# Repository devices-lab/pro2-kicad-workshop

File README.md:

# PCB design walkthrough with KiCad workshop

## Tasks

You are given the task of extending the solder:bit Gamepad boards with more NeoPixels. A design review has highlighted that we need more blinking lights than the 5x5 LED matrix on the micro:bit can supply!

1. Download the existing design files by cloning this repository.
2. Get familiar with the NeoPixel (WS2812B) datasheet and the exisiting schematic for version 0.5.
3. Open up KiCad, and begin with the Schematic Editor - adding symbols, assiginging footprints, adding values, etc.
4. Move onto the PCB Editor and import the changes from the schematic - moving footprints, routing, zone filling, DRC, etc.
5. Build a bill of materials (BOM) and a set of Gerber fabrication files for the next workshop!
6. Use Git for version control of your KiCad project.

Don’t worry if you don’t manage to get all the steps here completed, as we also supply a set of completed production files (BOM and Gerber files) in the same repository which can be used for the next session.

## Handy web links

- [solder:bit Gamepad repository](https://github.com/devices-lab/solderbit-gamepad)
- [KiCad 8.0 documentation](https://docs.kicad.org/8.0/en/)
- [Git cheat sheet](https://education.github.com/git-cheat-sheet-education.pdf)

## Credits

Thanks to [Dr John Vidler](https://github.com/JohnVidler) and [Aron Eggens](https://github.com/mac-aron), the Computing and Communications departement at Lancaster University, and everyone at the [Devices Lab](https://github.com/devices-lab).

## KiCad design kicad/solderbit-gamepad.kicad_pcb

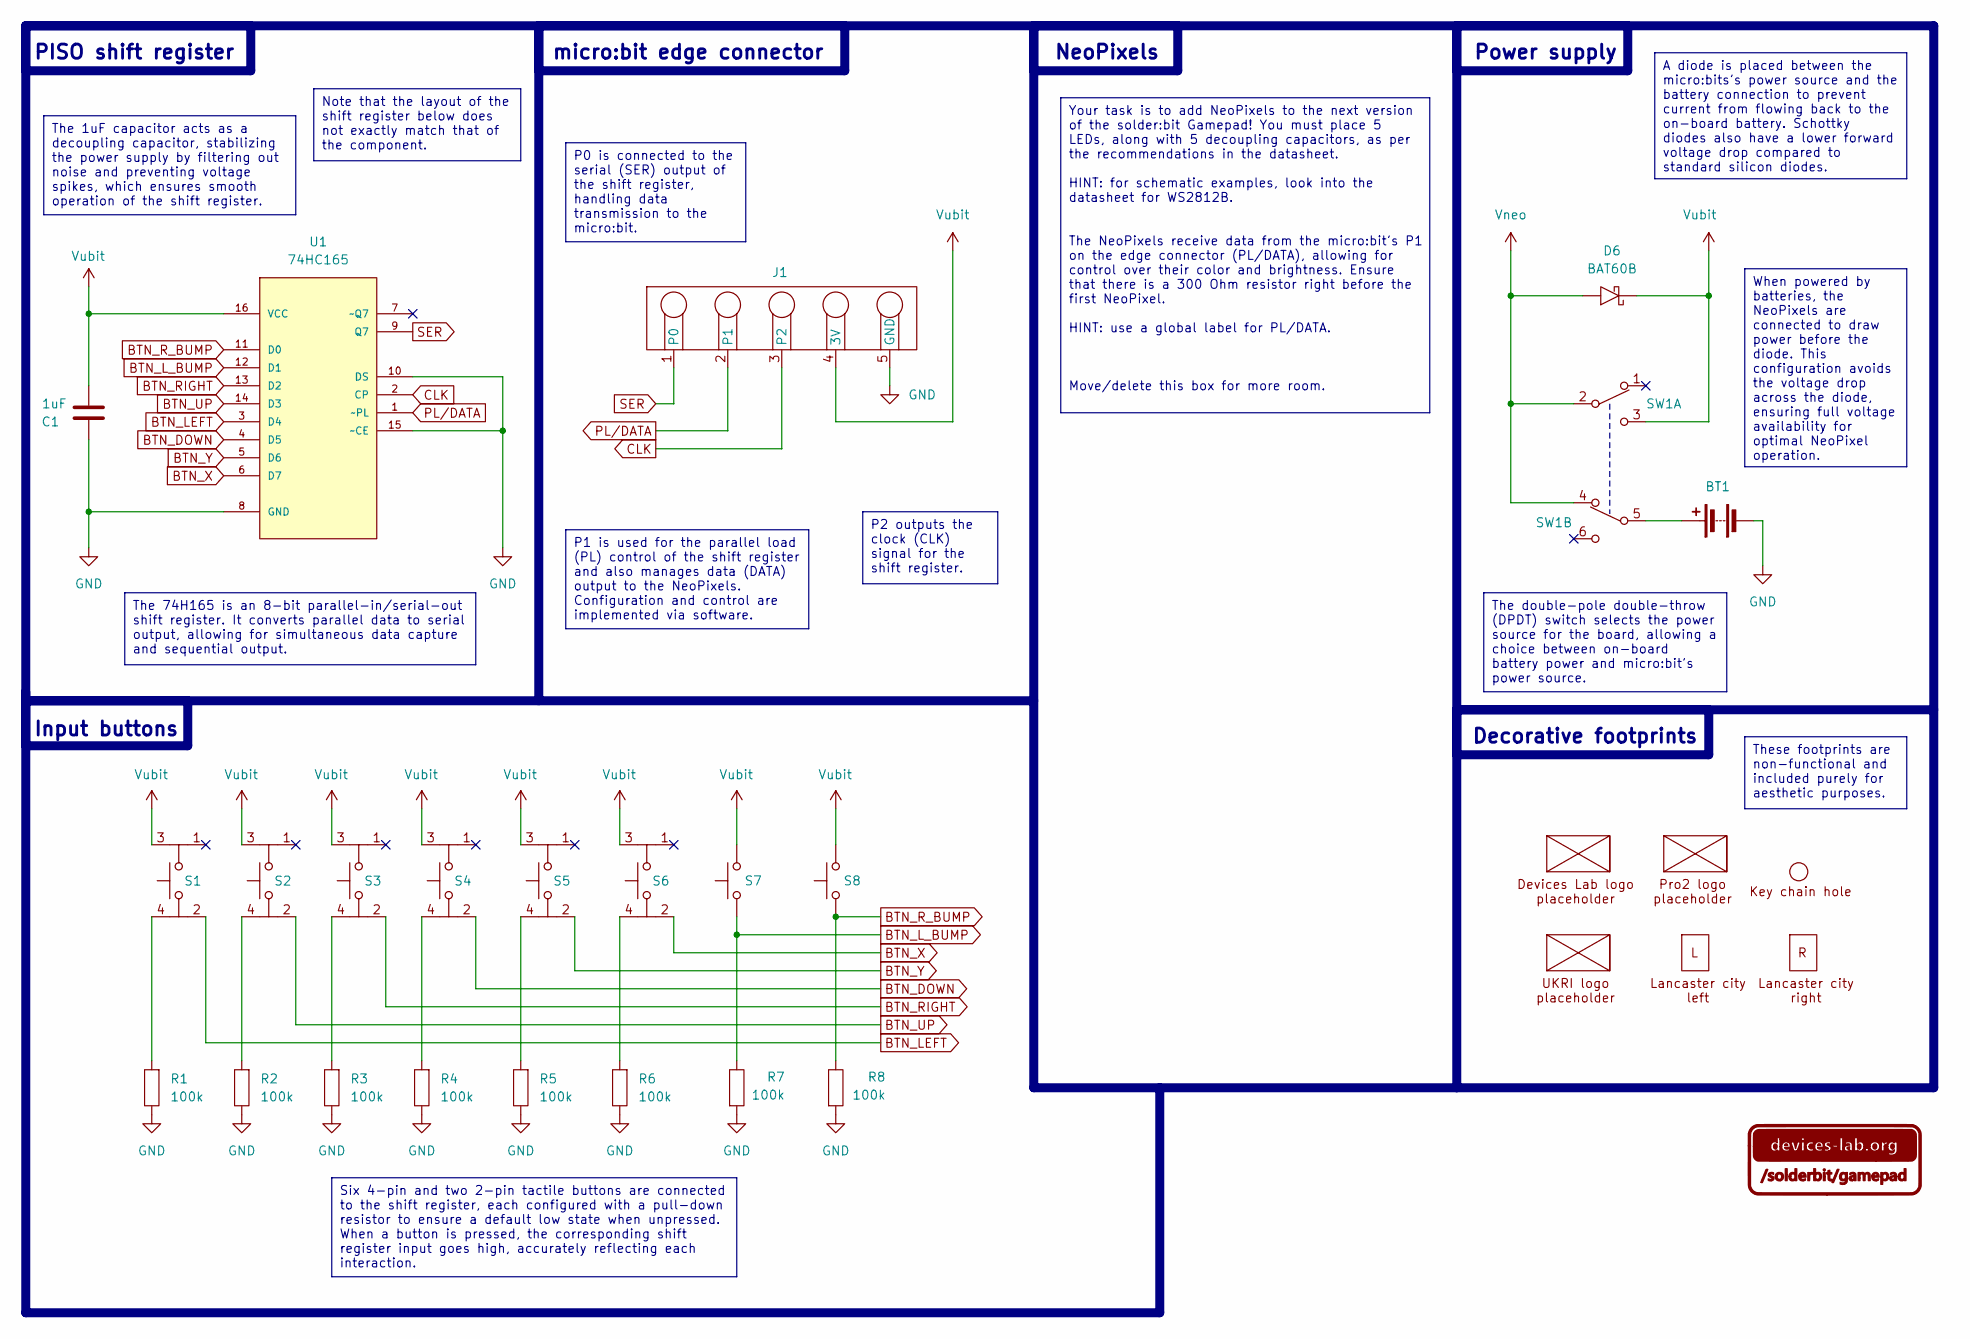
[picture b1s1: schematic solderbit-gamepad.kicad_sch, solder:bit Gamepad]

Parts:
BT1: BH-AAA-B5AA001; Battery_Holder
C1: 1uF; 1206_Capacitor
D6: BAT60B; Schottky_Diode_SOD-323
G1: Devices-Lab_Logo_H9mm
G2: Pro2_Logo
G3: Key_Chain_Hole
G4: UKRI_Logo
G5: LSS_L
G6: LSS_R
J1: Microbit; Microbit_Edge_Connector
R1, R2, R3, R4, R5, R6, R7, R8: 100k; 1206_Resistor
S1, S2, S3, S4, S5, S6: TS-1002S-AR06026; Tactile_Switch
S7: TS-1037-A4B3-D2; Tactile_Switch_Left_90_Degrees
S8: TS-1037-A4B3-D2; Tactile_Switch_Right_90_Degrees
SW1: MST22D18G2 125; Sliding_Switch_DPDT
U1: 74HC165; Shift_Register_74HC165D

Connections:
BTN_DOWN: S4.2, U1.4 (D5)
BTN_LEFT: S1.2, U1.3 (D4)
BTN_L_BUMP: R7.2, S7.2, U1.12 (D1)
BTN_RIGHT: S3.2, U1.13 (D2)
BTN_R_BUMP: R8.2, S8.2, U1.11 (D0)
BTN_UP: S2.2, U1.14 (D3)
BTN_X: S6.2, U1.6 (D7)
BTN_Y: S5.2, U1.5 (D6)
CLK: J1.3 (P2), U1.2 (CP)
GND: BT1.2 (-), C1.1, J1.5 (GND), R1.2, R2.2, R3.2, R4.2, R5.2, R6.2, R7.1, R8.1, U1.8 (GND), U1.10 (DS), U1.15 (~CE)
unnamed: BT1.1 (+), SW1.5 (B)
unnamed: R1.1, S1.4
unnamed: R2.1, S2.4
unnamed: R3.1, S3.4
unnamed: R4.1, S4.4
unnamed: R5.1, S5.4
unnamed: R6.1, S6.4
PL/DATA: J1.2 (P1), U1.1 (~PL)
SER: J1.1 (P0), U1.9 (Q7)
Vneo: D6.2 (A), SW1.2 (B), SW1.4 (A)
Vubit: C1.2, D6.1 (K), J1.4 (3V), S1.3, S2.3, S3.3, S4.3, S5.3, S6.3, S7.1, S8.1, SW1.3 (C), U1.16 (VCC)

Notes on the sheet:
P0 is connected to the serial (SER) output of the shift register, handling data transmission to the micro:bit.
When powered by batteries, the NeoPixels are connected to draw power before the diode. This configuration avoids the voltage drop across the diode, ensuring full voltage availability for optimal NeoPixel operation.
P2 outputs the clock (CLK) signal for the shift register.
P1 is used for the parallel load (PL) control of the shift register and also manages data (DATA) output to the NeoPixels. Configuration and control are implemented via software.
The 74H165 is an 8-bit parallel-in/serial-out shift register. It converts parallel data to serial output, allowing for simultaneous data capture and sequential output.
Your task is to add NeoPixels to the next version of the solder:bit Gamepad! You must place 5 LEDs, along with 5 decoupling capacitors, as per the recommendations in the datasheet. HINT: for schematic examples, look into the datasheet for WS2812B. The NeoPixels receive data from the micro:bit's P1 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
The double-pole double-throw (DPDT) switch selects the power source for the board, allowing a choice between on-board battery power and micro:bit's power source.
Six 4-pin and two 2-pin tactile buttons are connected to the shift register, each configured with a pull-down resistor to ensure a default low state when unpressed. When a button is pressed, the corresponding shift register input goes high, accurately reflecting each interaction.
These footprints are non-functional and included purely for aesthetic purposes.
A diode is placed between the micro:bits's power source and the battery connection to prevent current from flowing back to the on-board battery. Schottky diodes also have a lower forward voltage drop compared to standard silicon diodes.
The 1uF capacitor acts as a decoupling capacitor, stabilizing the power supply by filtering out noise and preventing voltage spikes, which ensures smooth operation of the shift register.
Note that the layout of the shift register below does not exactly match that of the component.
NeoPixels
Input buttons
Power supply
micro:bit edge connector
Decorative footprints
PISO shift register

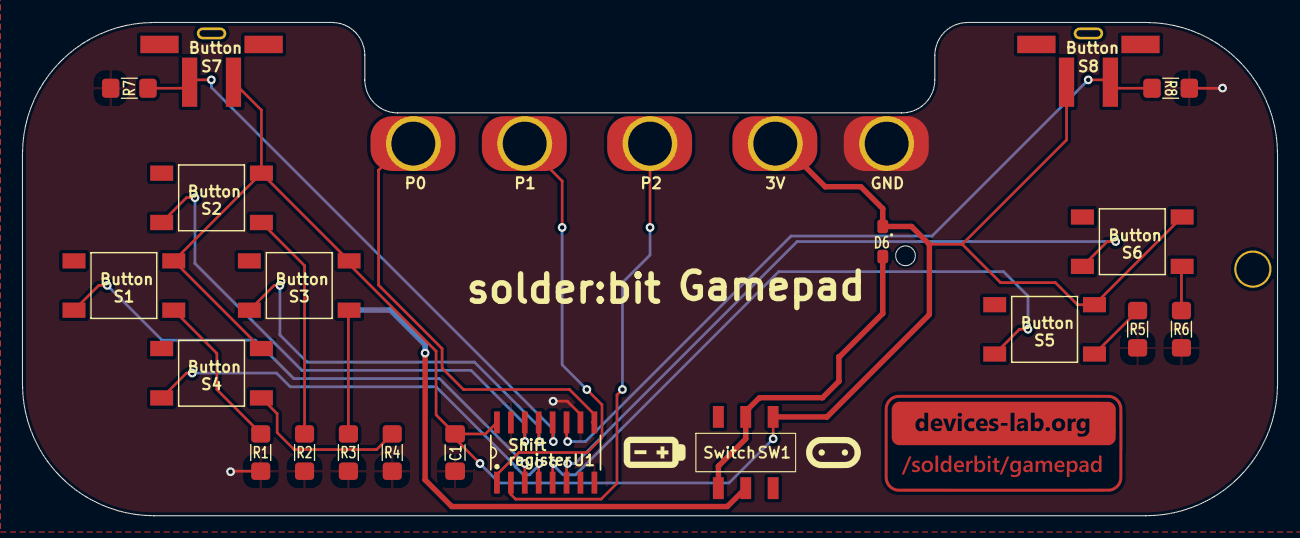
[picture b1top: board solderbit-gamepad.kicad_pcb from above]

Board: 2 copper layers, 114.5 x 45.0 mm, 28 parts (0 on the bottom side), 21 nets.

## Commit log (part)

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2024-07-03 Added KiCad files based on v0.6
2024-07-05 KiCad font fixes and 3D renders
2024-07-05 Updated gitignore, removed spurious DS_Store and removed neopixel busbar
2024-07-05 FONT fixes
2024-07-10 Final touches and fixes, and updated README.md
2024-07-10 README.md update
2024-07-10 Fixed fonts finally
2024-08-15 Uploaded the slide deck from the Pro2 event
